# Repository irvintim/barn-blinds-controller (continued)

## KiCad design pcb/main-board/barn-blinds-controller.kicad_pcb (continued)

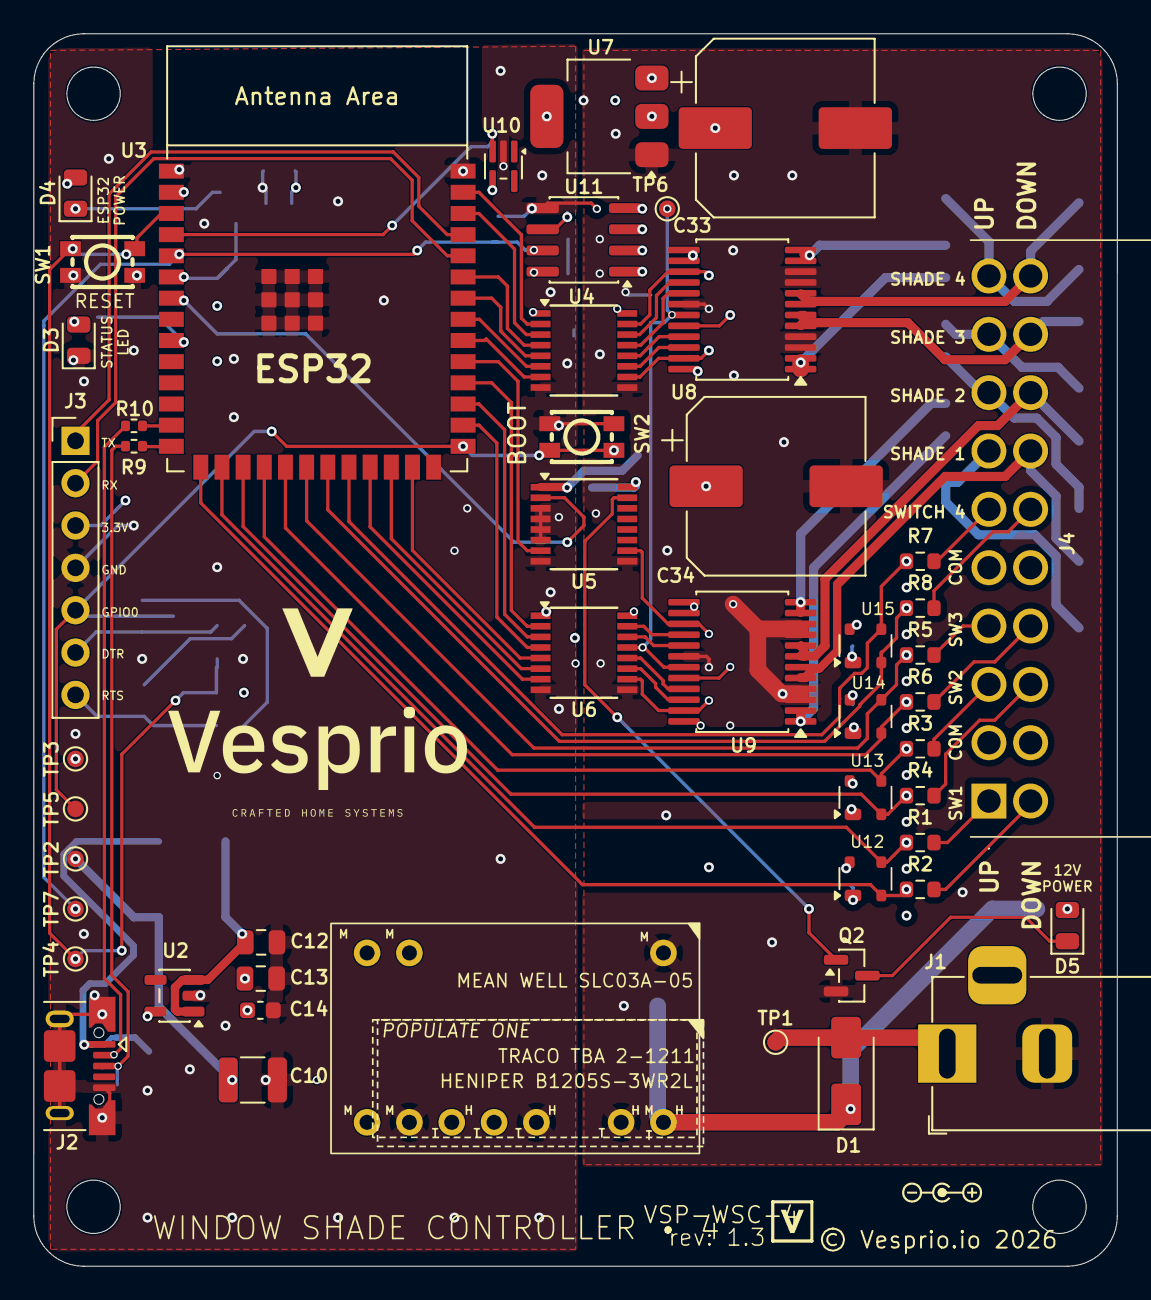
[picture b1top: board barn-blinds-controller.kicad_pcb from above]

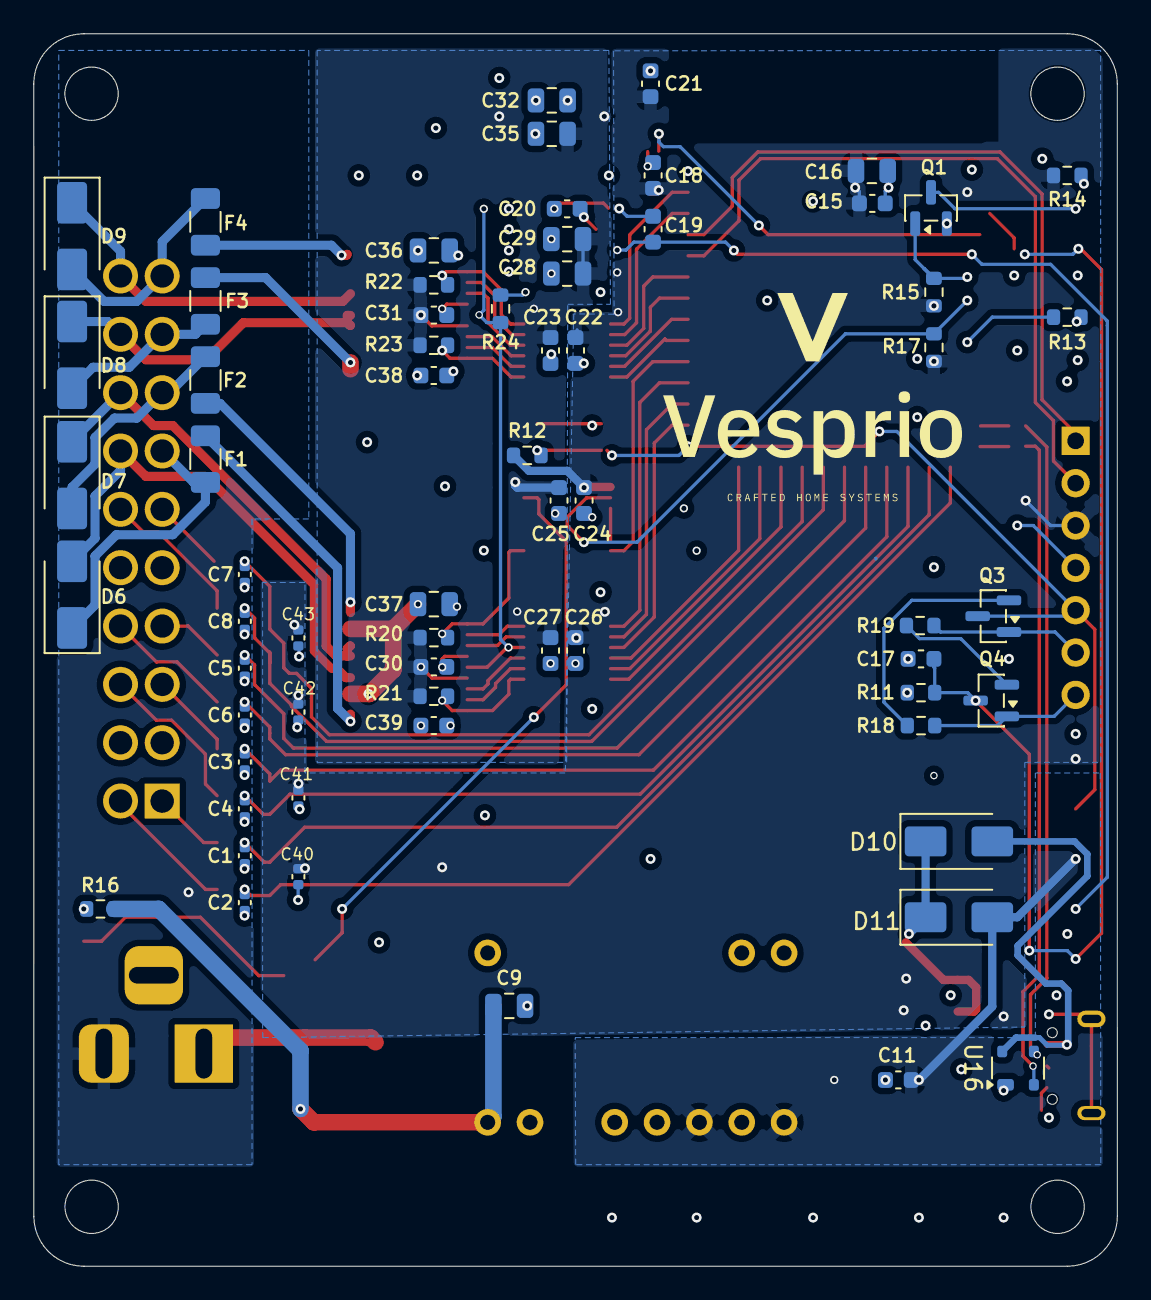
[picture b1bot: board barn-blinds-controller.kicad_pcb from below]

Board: 4 copper layers, 65.0 x 73.9 mm, 118 parts (65 on the bottom side), 88 nets.

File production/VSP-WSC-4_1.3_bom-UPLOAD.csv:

Designator,Footprint,Quantity,Value,LCSC Part #
"C1, C2, C3, C4, C5, C6, C7, C8, C40, C41, C42, C43",0402,12,100nF,C1525
C10,1210,1,100uF 16V,C7432790
"C11, C14, C15, C18, C21, C22, C23, C24, C25, C26, C27, C30, C31, C38, C39",0603,15,0.1uF / 0.1uF 25V,C1590
"C12, C16, C28, C29",0805,4,10uF 10V,C17024
"C13, C35",0805,2,22uF 10V,C29277
C17,0603,1,1uF,C15849
C19,0603,1,10nF 10V,C519405
C20,0603,1,1nF 10V,C519402
"C32, C36, C37",0805,3,10uF 25V,C15850
"C33, C34",CP_Elec_10x10.5,2,1000uF 25V,C7471896
C9,0805,1,22uF 25V,C45783
D1,D_SMA,1,SS54,C22452
"D10, D11",D_SMA,2,SS34,C8678
D3,0805,1,Red,C84256
D4,0805,1,White,C84258
D5,0805,1,Blue,C2293
"D6, D7, D8, D9",D_SMA,4,SMAJ15CA,C223985
"F1, F2, F3, F4",1206,4,Polyfuse 1206L110/16NR,C7542961
J1,BarrelJack_Horizontal,1,DC005-T20,C111567
J2,USB_Micro-B_XKB_U254-051T-4BH83-F1S,1,USB_B_Micro,C397452
J4,1786918,1,Phoenix Contact 1786918,C6652293
"Q1, Q2",SOT-23,2,2N7002,C8545
"Q3, Q4",SOT-23,2,S8050,C2146
"R1, R2, R3, R4, R5, R6, R7, R8, R14",0603,9,1k,C14676
"R9, R10",0402,2,22R,C25092
"R11, R12, R15, R17, R18, R19, R20, R21, R22, R23, R24",0603,11,10K,C25804
R13,0603,1,330R,C23138
R16,0603,1,1.8K,C4177
"SW1, SW2",SW-SMD_4P-L3.5-W3.0-P1.50-LS4.7,2,RESET / BOOT,C51927445
U1,DCDC_HYBRID_SLC03_TEC2,1,DCDC Converter,C20622657
U10,SOT-353_SC-70-5,1,TMP235,C2861437
U11,SOIC-8_3.9x4.9mm_P1.27mm,1,ACS725LLCTR-05AB-T,C3684552
"U12, U13, U14, U15, U16",SOT-143,5,PRTR5V0U2X,C5158049
U2,SOT-23-5,1,AP2112K-3.3,C23380830
U3,ESP32-S3-WROOM-1,1,ESP32-S3-WROOM-1,C2913197
"U4, U5, U6",SSOP-16_3.9x4.9mm_P0.635mm,3,ISO7760DBQ,C2868628
U7,SOT-223-3_TabPin2,1,AMS1117-3.3,C6186
"U8, U9",SSOP-24_5.3x8.2mm_P0.65mm,2,TB6612FNG,C88224

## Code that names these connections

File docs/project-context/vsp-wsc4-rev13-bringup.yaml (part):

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# pinout -- do not flash that to a Rev 1.3 board, every motor GPIO moved).
#
# Pinout source of truth: "Rev 1.3 GPIO Map" in vsp-wsc4-todo.md, plus the
# GPIO6/GPIO7 LED assignment from CLAUDE.md (added after that map was written).
#
# SAFETY: motor STBY defaults OFF, so the TB6612FNG outputs are in high-Z at
# boot. Nothing can drive a motor until you deliberately flip "Motor Enable".
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
logger:
  level: DEBUG
  # The S3's built-in USB-Serial-JTAG peripheral (GPIO19/20) -- this is what
  # J2 connects to. Without this you get no console over the native USB port.
  hardware_uart: USB_SERIAL_JTAG

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output:
  # --- Motor driver standby (through isolator U6) ---
  - platform: gpio
    pin: GPIO35
    id: motor_stby

  # --- Direction pins: TB6612FNG IN1/IN2 via isolators ---
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
  # Shade 1 = J4 pins 7/17  (U9 ch A, driven by the ISO_SH2_* nets)
  - platform: gpio
    pin: GPIO48
    id: sh1_open
  - platform: gpio
    pin: GPIO47
    id: sh1_closed
  # Shade 2 = J4 pins 8/18  (U9 ch B, driven by the ISO_SH1_* nets)
  - platform: gpio
    pin: GPIO36
    id: sh2_open
  - platform: gpio
    pin: GPIO37
    id: sh2_closed
  # Shade 3 = J4 pins 9/19  (U8 ch A, driven by the ISO_SH4_* nets)
  - platform: gpio
    pin: GPIO41
    id: sh3_open
  - platform: gpio
    pin: GPIO40
    id: sh3_closed
  # Shade 4 = J4 pins 10/20 (U8 ch B, driven by the ISO_SH3_* nets)
  - platform: gpio
    pin: GPIO42
    id: sh4_open
  - platform: gpio
    pin: GPIO2
    id: sh4_closed

  # --- On-board LEDs ---
  # D3 (red) is the status LED, driven directly by the ESP32.
  - platform: gpio
    pin: GPIO16
    id: out_d3
  # D4/D5 gate 2N7002 FETs whose gates are pulled up to their rails, so the
  # resting state is ON and the GPIO only ever pulls them down:
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  # D5's gate crosses the isolation barrier through spare U5 channel A, and
  # D5 feeds from +12V_RAW so its current bypasses the ACS725 measurement.
  - platform: gpio
    pin: GPIO6
    id: out_d4
  - platform: gpio
    pin: GPIO7
    id: out_d5

  # --- PWM (speed) pins. LEDC so duty is measurable as an average voltage. ---
  # Same channel cross as the direction pins above -- named by J4 terminal.
  - platform: ledc
    pin: GPIO21          # Shade 1, J4 7/17  (ISO_SH2_PWM)
    id: sh1_pwm
    frequency: 20000Hz
  - platform: ledc
    pin: GPIO38          # Shade 2, J4 8/18  (ISO_SH1_PWM)
    id: sh2_pwm
    frequency: 20000Hz
  - platform: ledc
    pin: GPIO39          # Shade 3, J4 9/19  (ISO_SH4_PWM)
    id: sh3_pwm
    frequency: 20000Hz
  - platform: ledc
    pin: GPIO1           # Shade 4, J4 10/20 (ISO_SH3_PWM)
    id: sh4_pwm
    frequency: 20000Hz

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# `inverted: true` -- "on" here means the input is being pulled to GND).
#
# With nothing connected, all 8 must read OFF. If any reads ON or flickers,
# that pin's pull-up is not working -- see the bring-up notes on GPIO46.
# To test: jumper the J4 pin to an adjacent GND_ISO pin (2, 5, 12, or 15).
# =============================================================================
binary_sensor:
  - platform: gpio
    name: "SW1 Up (GPIO46)"
    pin: { number: GPIO46, mode: { input: true, pullup: true }, inverted: true }
  - platform: gpio
    name: "SW1 Down (GPIO3)"
    pin: { number: GPIO3, mode: { input: true, pullup: true }, inverted: true }
  - platform: gpio
    name: "SW2 Up (GPIO10)"
    pin: { number: GPIO10, mode: { input: true, pullup: true }, inverted: true }
  - platform: gpio
    name: "SW2 Down (GPIO9)"
    pin: { number: GPIO9, mode: { input: true, pullup: true }, inverted: true }
  - platform: gpio
    name: "SW3 Up (GPIO12)"
    pin: { number: GPIO12, mode: { input: true, pullup: true }, inverted: true }
  - platform: gpio
    name: "SW3 Down (GPIO11)"
    pin: { number: GPIO11, mode: { input: true, pullup: true }, inverted: true }
  - platform: gpio
    name: "SW4 Up (GPIO14)"
    pin: { number: GPIO14, mode: { input: true, pullup: true }, inverted: true }
  - platform: gpio
    name: "SW4 Down (GPIO13)"
    pin: { number: GPIO13, mode: { input: true, pullup: true }, inverted: true }

# =============================================================================
# SENSORS
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  # --- TMP235 analog temperature sensor ---
  # On-board, so it reads with nothing connected. Should track room ambient.
  - platform: adc
    pin: GPIO4
    name: "TMP235 raw volts"
    id: tmp235_raw
    update_interval: 5s
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  # should sit near 1.65 V. A raw reading far from that at idle points at the
  # sensor's supply or offset rather than at the formula.
  - platform: adc
    pin: GPIO5
    name: "ACS725 raw volts"
    id: acs725_raw
    update_interval: 500ms
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      - logger.log: "LED test complete -- D4/D5 restored to their power-on state"

  # Walks every motor direction pin one at a time so you can follow along on
  # the driver-side pins with a meter. STBY is left alone; run it either way.
  - platform: template
    name: "TEST: Walk motor direction pins"
    on_press:
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      - output.turn_off: sh4_open
      - output.turn_off: sh4_closed

      - logger.log: "-> Shade 1 OPEN  J4.7  (GPIO48)"
      - output.turn_on: sh1_open
      - delay: 2s
      - output.turn_off: sh1_open
      - logger.log: "-> Shade 1 CLOSED J4.17 (GPIO47)"
      - output.turn_on: sh1_closed
      - delay: 2s
      - output.turn_off: sh1_closed

      - logger.log: "-> Shade 2 OPEN  J4.8  (GPIO36)"
      - output.turn_on: sh2_open
      - delay: 2s
      - output.turn_off: sh2_open
      - logger.log: "-> Shade 2 CLOSED J4.18 (GPIO37)"
      - output.turn_on: sh2_closed
      - delay: 2s
      - output.turn_off: sh2_closed

      - logger.log: "-> Shade 3 OPEN  J4.9  (GPIO41)"
      - output.turn_on: sh3_open
      - delay: 2s
      - output.turn_off: sh3_open
      - logger.log: "-> Shade 3 CLOSED J4.19 (GPIO40)"
      - output.turn_on: sh3_closed
      - delay: 2s
      - output.turn_off: sh3_closed

      - logger.log: "-> Shade 4 OPEN  J4.10 (GPIO42)"
      - output.turn_on: sh4_open
      - delay: 2s
      - output.turn_off: sh4_open
      - logger.log: "-> Shade 4 CLOSED J4.20 (GPIO2)"
      - output.turn_on: sh4_closed
      - delay: 2s
      - output.turn_off: sh4_closed
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
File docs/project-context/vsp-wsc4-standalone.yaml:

substitutions:
  device_name: shade-controller
  friendly_name: Shade Controller

esphome:
  name: ${device_name}
  friendly_name: ${friendly_name}
  name_add_mac_suffix: true  # makes each device unique: shade-controller-a1b2c3
  project:
    name: "Vesprio.WSC-4"
    version: "1.2"
  on_boot:
    priority: 700
    then:
      - output.turn_on: motor_stby

esp32:
  board: esp32-s3-devkitc-1
  framework:
    type: esp-idf

wifi:
  ap:
    ssid: "Shade Controller Setup"
    password: "shadectrl"

improv_ble:

captive_portal:

# Uncomment and fill in after WiFi is configured via Improv BLE
# wifi:
#   ssid: !secret wifi_ssid
#   password: !secret wifi_password

api:
  encryption:
    key: !secret api_key

ota:
  - platform: esphome
    password: !secret ota_password

logger:

web_server:
  port: 80
  version: 3

status_led:
  pin: GPIO16

output:
  - platform: gpio
    pin: GPIO37
    id: motor_stby

  - platform: gpio
    pin: GPIO43
    id: shade1_open
  - platform: gpio
    pin: GPIO2
    id: shade1_close

  - platform: gpio
    pin: GPIO44
    id: shade2_open
  - platform: gpio
    pin: GPIO42
    id: shade2_close

  - platform: gpio
    pin: GPIO36
    id: shade3_open
  - platform: gpio
    pin: GPIO35
    id: shade3_close

  - platform: gpio
    pin: GPIO38
    id: shade4_open
  - platform: gpio
    pin: GPIO39
    id: shade4_close

cover:
  - platform: time_based
    name: "Shade 1"
    id: shade_1
    open_action:
      - output.turn_on: shade1_open
      - output.turn_off: shade1_close
    open_duration: 60s
    close_action:
      - output.turn_on: shade1_close
      - output.turn_off: shade1_open
    close_duration: 60s
    stop_action:
      - output.turn_off: shade1_open
      - output.turn_off: shade1_close

  - platform: time_based
    name: "Shade 2"
    id: shade_2
    open_action:
      - output.turn_on: shade2_open
      - output.turn_off: shade2_close
    open_duration: 60s
    close_action:
      - output.turn_on: shade2_close
      - output.turn_off: shade2_open
    close_duration: 60s
    stop_action:
      - output.turn_off: shade2_open
      - output.turn_off: shade2_close

  - platform: time_based
    name: "Shade 3"
    id: shade_3
    open_action:
      - output.turn_on: shade3_open
      - output.turn_off: shade3_close
    open_duration: 60s
    close_action:
      - output.turn_on: shade3_close
      - output.turn_off: shade3_open
    close_duration: 60s
    stop_action:
      - output.turn_off: shade3_open
      - output.turn_off: shade3_close

  - platform: time_based
    name: "Shade 4"
    id: shade_4
    open_action:
      - output.turn_on: shade4_open
      - output.turn_off: shade4_close
    open_duration: 60s
    close_action:
      - output.turn_on: shade4_close
      - output.turn_off: shade4_open
    close_duration: 60s
    stop_action:
      - output.turn_off: shade4_open
      - output.turn_off: shade4_close

button:
  - platform: template
    name: "All Open"
    on_press:
      - cover.control:
          id: shade_1
          position: 1.0
      - delay: 200ms
      - cover.control:
          id: shade_2
          position: 1.0
      - delay: 200ms
      - cover.control:
          id: shade_3
          position: 1.0
      - delay: 200ms
      - cover.control:
          id: shade_4
          position: 1.0

  - platform: template
    name: "All Close"
    on_press:
      - cover.control:
          id: shade_1
          position: 0.0
      - delay: 200ms
      - cover.control:
          id: shade_2
          position: 0.0
      - delay: 200ms
      - cover.control:
          id: shade_3
          position: 0.0
      - delay: 200ms
      - cover.control:
          id: shade_4
          position: 0.0

  - platform: template
    name: "All Stop"
    on_press:
      - cover.stop: shade_1
      - cover.stop: shade_2
      - cover.stop: shade_3
      - cover.stop: shade_4

sensor:
  - platform: adc
    pin: GPIO14
    name: "Motor Current"
    id: motor_current
    update_interval: 100ms
    attenuation: 12db
    device_class: current
    filters:
      - sliding_window_moving_average:
          window_size: 5
          send_every: 5
      - lambda: 'return (x - 1.65) / 0.4;'
    unit_of_measurement: "A"
    on_value:
      then:
        - if:
            condition:
              lambda: 'return x > 1.4;'
            then:
              - logger.log: "Stall detected -- stopping all shades"
              - cover.stop: shade_1
              - cover.stop: shade_2
              - cover.stop: shade_3
              - cover.stop: shade_4

  - platform: adc
    pin: GPIO15
    name: "Controller Temperature"
    id: controller_temp
    update_interval: 10s
    attenuation: 12db
    device_class: temperature
    filters:
      - lambda: 'return (x - 0.5) / 0.01;'
    unit_of_measurement: "°C"

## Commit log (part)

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2026-04-15 Updated capacitor direction
2026-04-15 Added hierarchical sheets for custom pcb design
2026-04-16 adding DCDC converter symbol and footprint
2026-04-17 adding hierachical sheets: Isolated circuits, esp32, etc
2026-04-18 Started running traces
2026-04-19 PCB tracing complete
2026-04-20 Reworking with new terminal block, adding mounting holes. Need to rerun a number of traces.
2026-04-21 Finishing touches
2026-04-23 BOM work
2026-04-23 Added BOM
2026-04-23 Updated BOM, fixed a few components
2026-04-23 Replaced fuses and rearranged to fit better
2026-04-23 noop
2026-04-23 3d model for 8 port connector
2026-04-23 Updated connector to match actual footprint, updated 3D images.
2026-04-24 Final cleanup
2026-04-24 Sent for production
2026-04-28 Refactored board to use larger vias and route better paths.
2026-04-28 Added revision text to board
2026-06-11 V 1.2
2026-06-12 1st pass at Claude adding new input circuits.
2026-06-28 Rev 1.3 updates
2026-06-30 DIN rail options.
2026-06-30 Updated project AI memory
2026-06-30 added switch_inputs
2026-06-30 added power_icon
